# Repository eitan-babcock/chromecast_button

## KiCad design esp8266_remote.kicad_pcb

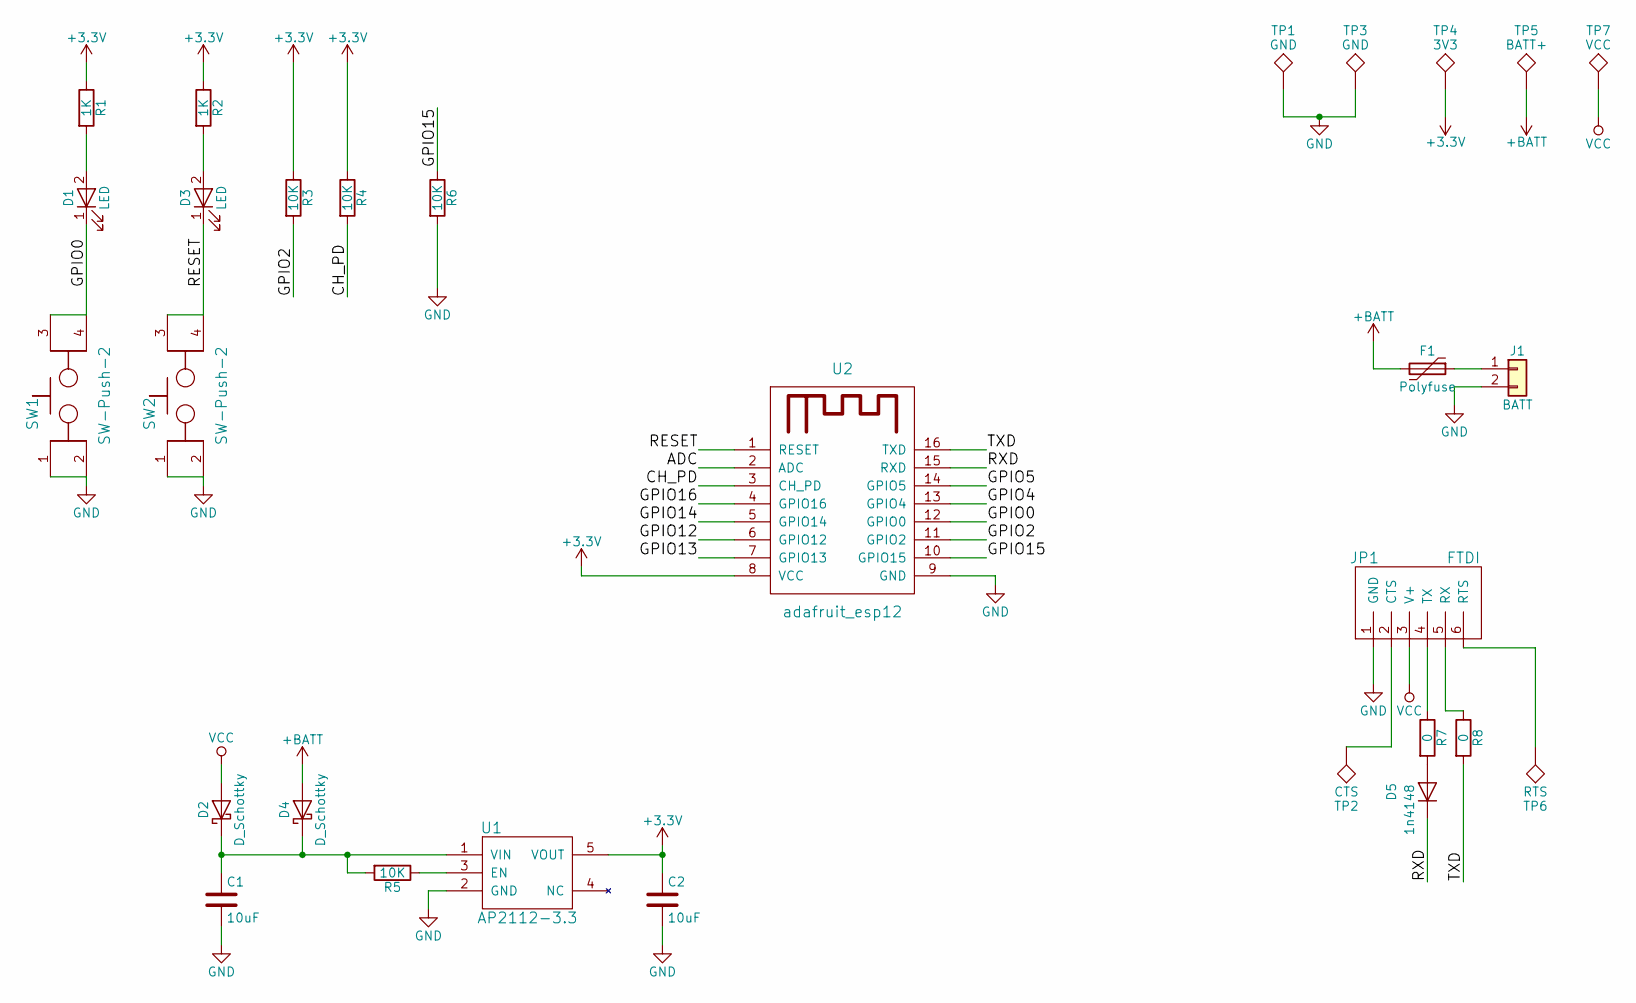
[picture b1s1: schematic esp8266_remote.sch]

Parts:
C1, C2: 10uF; C_0805_HandSoldering
D1: LED; LED_0805_HandSoldering
D2, D4: D_Schottky; MBR120_SCHOTTSKY_DIODE
D3: LED; LED_D3.0mm
D5: 1n4148; 1N4148W_SIGNAL_DIODE
F1: Polyfuse; MSMF050_FUSE
J1: BATT; JST_PH_S2B-PH-K_02x2.00mm_Angled
JP1: FTDI; Pin_Header_Straight_1x06_Pitch2.54mm
R1, R2: 1K; R_0805_HandSoldering
R3, R4, R5, R6: 10K; R_0805_HandSoldering
R7, R8: 0; R_0805_HandSoldering
SW1: SW-Push-2; KMR2_switch
SW2: SW-Push-2; TL1100_SWITCH
TP1, TP3: GND; Measurement_Point_Square-TH_Small
TP2: CTS; Measurement_Point_Round-TH_Small
TP4: 3V3; Measurement_Point_Round-TH_Small
TP5: BATT+; Measurement_Point_Round-TH_Small
TP6: RTS; Measurement_Point_Round-TH_Small
TP7: VCC; Measurement_Point_Round-TH_Small
U1: AP2112-3.3; AP2112-SOT25
U2: adafruit_esp12

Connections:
+3V3: C2.1, R1.1, R2.1, R3.1, R4.1, TP4.1, U1.5 (VOUT), U2.8 (VCC)
+BATT: D4.2 (A), F1.2, TP5.1
/ADC: U2.2 (ADC)
/CH_PD: R4.2, U2.3 (CH_PD)
/GPIO0: D1.1 (K), SW1.3, SW1.4, U2.12 (GPIO0)
/GPIO2: R3.2, U2.11 (GPIO2)
/GPIO4: U2.13 (GPIO4)
/GPIO5: U2.14 (GPIO5)
/GPIO12: U2.6 (GPIO12)
/GPIO13: U2.7 (GPIO13)
/GPIO14: U2.5 (GPIO14)
/GPIO15: R6.1, U2.10 (GPIO15)
/GPIO16: U2.4 (GPIO16)
/RESET: D3.1 (K), SW2.3, SW2.4, U2.1 (RESET)
/RXD: D5.1 (K), U2.15 (RXD)
/TXD: R8.2, U2.16 (TXD)
GND: C1.2, C2.2, J1.2, JP1.1 (GND), R6.2, SW1.1, SW1.2, SW2.1, SW2.2, TP1.1, TP3.1, U1.2 (GND), U2.9 (GND)
unnamed: C1.1, D2.1 (K), D4.1 (K), R5.2, U1.1 (VIN)
unnamed: D1.2 (A), R1.2
unnamed: D3.2 (A), R2.2
unnamed: D5.2 (A), R7.2
unnamed: F1.1, J1.1
unnamed: JP1.2 (CTS), TP2.1
unnamed: JP1.4 (TX), R7.1
unnamed: JP1.5 (RX), R8.1
unnamed: JP1.6 (RTS), TP6.1
unnamed: R5.1, U1.3 (EN)
VCC: D2.2 (A), JP1.3 (V+), TP7.1

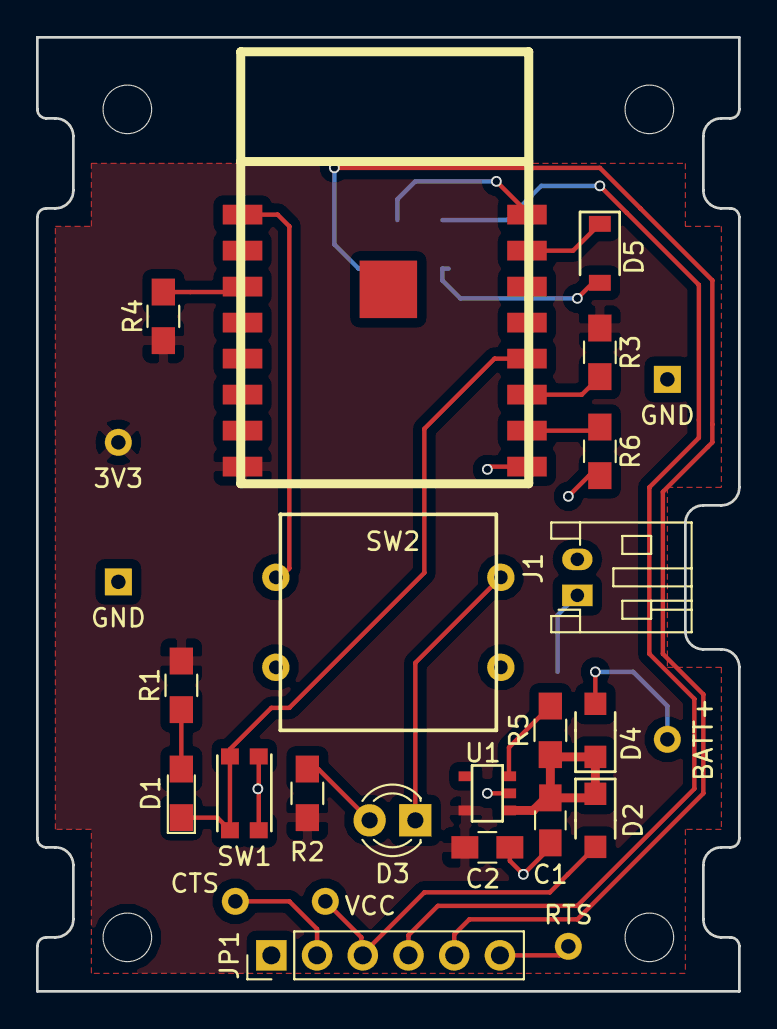
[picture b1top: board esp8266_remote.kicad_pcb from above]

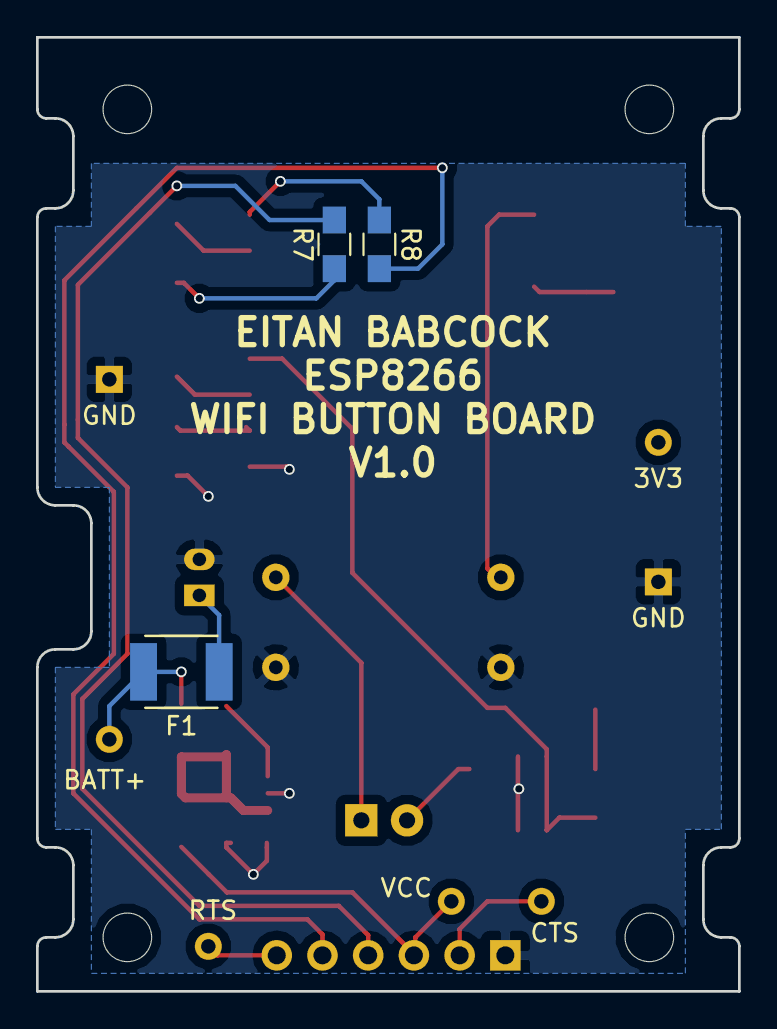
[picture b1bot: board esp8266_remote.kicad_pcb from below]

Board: 2 copper layers, 39.0 x 53.0 mm, 29 parts (3 on the bottom side), 21 nets.
